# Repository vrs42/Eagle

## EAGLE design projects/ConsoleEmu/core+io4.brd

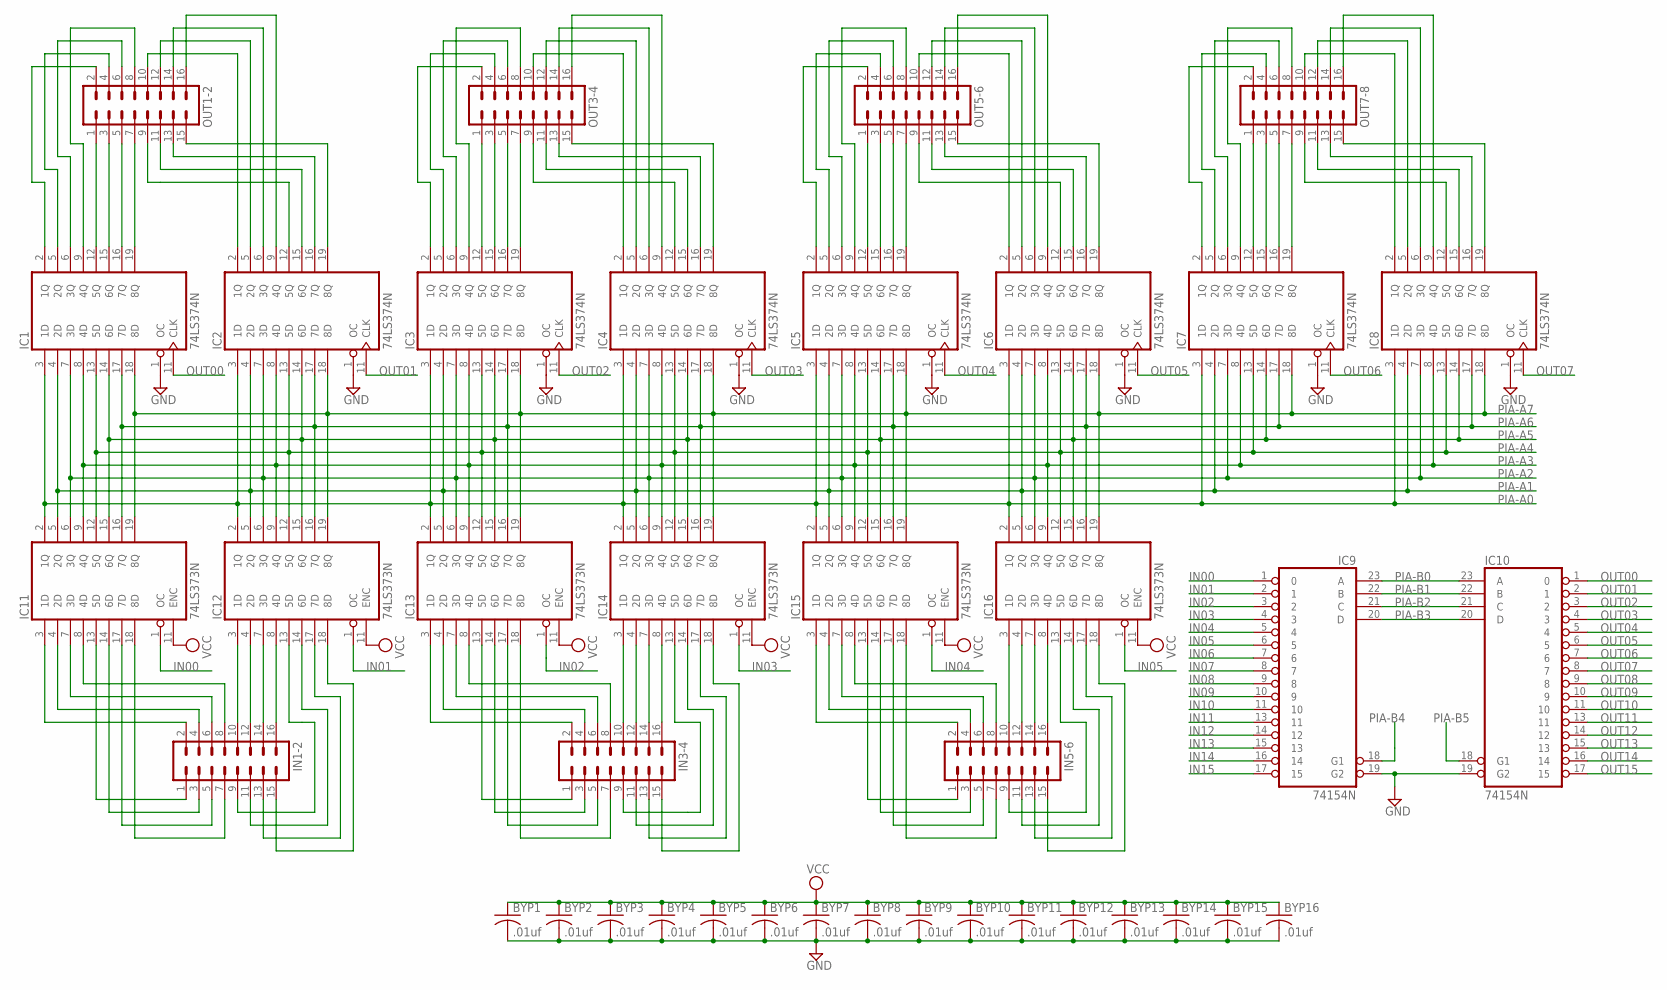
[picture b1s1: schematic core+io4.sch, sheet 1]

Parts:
BYP1, BYP2, BYP3, BYP4, BYP5, BYP6, BYP7, BYP8, BYP9, BYP10, BYP11, BYP12, BYP13, BYP14, BYP15, BYP16: .01uf; C050-025X075
IC1, IC2, IC3, IC4, IC5, IC6, IC7, IC8: 74LS374N; DIL20
IC9, IC10: 74154N; DIL24-6
IC11, IC12, IC13, IC14, IC15, IC16: 74LS373N; DIL20
IN1-2, IN3-4, IN5-6: MA08-2
OUT1-2, OUT3-4, OUT5-6, OUT7-8: MA08-2

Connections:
GND: BYP1.2, BYP2.2, BYP3.2, BYP4.2, BYP5.2, BYP6.2, BYP7.2, BYP8.2, BYP9.2, BYP10.2, BYP11.2, BYP12.2, BYP13.2, BYP14.2, BYP15.2, BYP16.2, IC1.1 (OC), IC1.10 (GND), IC2.1 (OC), IC2.10 (GND), IC3.1 (OC), IC3.10 (GND), IC4.1 (OC), IC4.10 (GND), IC5.1 (OC), IC5.10 (GND), IC6.1 (OC), IC6.10 (GND), IC7.1 (OC), IC7.10 (GND), IC8.1 (OC), IC8.10 (GND), IC9.12 (GND), IC9.19 (G2), IC10.12 (GND), IC10.19 (G2), IC11.10 (GND), IC12.10 (GND), IC13.10 (GND), IC14.10 (GND), IC15.10 (GND), IC16.10 (GND); also elsewhere on the board
IN00: IC9.1 (0), IC11.1 (OC)
IN01: IC9.2 (1), IC12.1 (OC)
IN02: IC9.3 (2), IC13.1 (OC)
IN03: IC9.4 (3), IC14.1 (OC)
IN04: IC9.5 (4), IC15.1 (OC)
IN05: IC9.6 (5), IC16.1 (OC)
IN06: IC9.7 (6)
IN07: IC9.8 (7)
IN08: IC9.9 (8)
IN09: IC9.10 (9)
IN10: IC9.11 (10)
IN11: IC9.13 (11)
IN12: IC9.14 (12)
IN13: IC9.15 (13)
IN14: IC9.16 (14)
IN15: IC9.17 (15)
unnamed: IC12.3 (1D), IN1-2.10
unnamed: IC12.4 (2D), IN1-2.12
unnamed: IC12.7 (3D), IN1-2.14
unnamed: IC12.8 (4D), IN1-2.16
unnamed: IC11.8 (4D), IN1-2.8
unnamed: IC11.7 (3D), IN1-2.6
unnamed: IC11.4 (2D), IN1-2.4
unnamed: IC11.3 (1D), IN1-2.2
unnamed: IC11.13 (5D), IN1-2.1
unnamed: IC11.14 (6D), IN1-2.3
unnamed: IC11.17 (7D), IN1-2.5
unnamed: IC11.18 (8D), IN1-2.7
unnamed: IC12.13 (5D), IN1-2.9
unnamed: IC12.14 (6D), IN1-2.11
unnamed: IC12.17 (7D), IN1-2.13
unnamed: IC12.18 (8D), IN1-2.15
unnamed: IC5.2 (1Q), OUT5-6.2
unnamed: IC14.3 (1D), IN3-4.10
unnamed: IC14.4 (2D), IN3-4.12
unnamed: IC14.7 (3D), IN3-4.14
unnamed: IC14.8 (4D), IN3-4.16
unnamed: IC3.12 (5Q), OUT3-4.1
unnamed: IC3.15 (6Q), OUT3-4.3
unnamed: IC3.16 (7Q), OUT3-4.5
unnamed: IC3.19 (8Q), OUT3-4.7
unnamed: IC13.3 (1D), IN3-4.2
unnamed: IC13.4 (2D), IN3-4.4
unnamed: IC13.7 (3D), IN3-4.6
unnamed: IC13.8 (4D), IN3-4.8
unnamed: IC14.13 (5D), IN3-4.9
unnamed: IC14.14 (6D), IN3-4.11
unnamed: IC14.17 (7D), IN3-4.13
unnamed: IC14.18 (8D), IN3-4.15
unnamed: IC13.13 (5D), IN3-4.1
unnamed: IC13.14 (6D), IN3-4.3
unnamed: IC13.17 (7D), IN3-4.5
unnamed: IC13.18 (8D), IN3-4.7
unnamed: IC3.5 (2Q), OUT3-4.4
unnamed: IC3.6 (3Q), OUT3-4.6
unnamed: IC3.2 (1Q), OUT3-4.2
unnamed: IC3.9 (4Q), OUT3-4.8
unnamed: IC1.12 (5Q), OUT1-2.1
unnamed: IC1.15 (6Q), OUT1-2.3
unnamed: IC1.16 (7Q), OUT1-2.5
unnamed: IC1.19 (8Q), OUT1-2.7
unnamed: IC1.2 (1Q), OUT1-2.2
unnamed: IC1.5 (2Q), OUT1-2.4
unnamed: IC1.6 (3Q), OUT1-2.6
unnamed: IC1.9 (4Q), OUT1-2.8
unnamed: IC2.19 (8Q), OUT1-2.15
unnamed: IC2.16 (7Q), OUT1-2.13
unnamed: IC2.15 (6Q), OUT1-2.11
unnamed: IC2.12 (5Q), OUT1-2.9
unnamed: IC2.2 (1Q), OUT1-2.10
unnamed: IC2.5 (2Q), OUT1-2.12
unnamed: IC2.6 (3Q), OUT1-2.14
unnamed: IC2.9 (4Q), OUT1-2.16
unnamed: IC4.2 (1Q), OUT3-4.10
unnamed: IC4.5 (2Q), OUT3-4.12
unnamed: IC4.6 (3Q), OUT3-4.14
unnamed: IC4.9 (4Q), OUT3-4.16
unnamed: IC4.19 (8Q), OUT3-4.15
unnamed: IC4.16 (7Q), OUT3-4.13
unnamed: IC4.15 (6Q), OUT3-4.11
unnamed: IC4.12 (5Q), OUT3-4.9
unnamed: IC16.3 (1D), IN5-6.10
unnamed: IC16.4 (2D), IN5-6.12
unnamed: IC16.7 (3D), IN5-6.14
unnamed: IC16.8 (4D), IN5-6.16
unnamed: IC5.12 (5Q), OUT5-6.1
unnamed: IC5.15 (6Q), OUT5-6.3
unnamed: IC5.16 (7Q), OUT5-6.5
unnamed: IC5.19 (8Q), OUT5-6.7
unnamed: IC7.12 (5Q), OUT7-8.1
unnamed: IC7.15 (6Q), OUT7-8.3
unnamed: IC7.16 (7Q), OUT7-8.5
unnamed: IC7.19 (8Q), OUT7-8.7
unnamed: IC5.5 (2Q), OUT5-6.4
unnamed: IC5.6 (3Q), OUT5-6.6
unnamed: IC5.9 (4Q), OUT5-6.8
unnamed: IC6.12 (5Q), OUT5-6.9
unnamed: IC6.15 (6Q), OUT5-6.11
unnamed: IC6.16 (7Q), OUT5-6.13
unnamed: IC6.19 (8Q), OUT5-6.15
unnamed: IC6.2 (1Q), OUT5-6.10
unnamed: IC6.5 (2Q), OUT5-6.12
unnamed: IC6.6 (3Q), OUT5-6.14
unnamed: IC6.9 (4Q), OUT5-6.16
unnamed: IC15.3 (1D), IN5-6.2
unnamed: IC15.4 (2D), IN5-6.4
unnamed: IC15.7 (3D), IN5-6.6
unnamed: IC15.8 (4D), IN5-6.8
unnamed: IC16.13 (5D), IN5-6.9
unnamed: IC16.14 (6D), IN5-6.11
unnamed: IC16.17 (7D), IN5-6.13
unnamed: IC16.18 (8D), IN5-6.15
unnamed: IC15.13 (5D), IN5-6.1
unnamed: IC15.14 (6D), IN5-6.3
unnamed: IC15.17 (7D), IN5-6.5
unnamed: IC15.18 (8D), IN5-6.7
unnamed: IC8.19 (8Q), OUT7-8.15
unnamed: IC8.16 (7Q), OUT7-8.13
unnamed: IC8.15 (6Q), OUT7-8.11
unnamed: IC8.12 (5Q), OUT7-8.9
unnamed: IC8.2 (1Q), OUT7-8.10
unnamed: IC8.5 (2Q), OUT7-8.12
unnamed: IC8.6 (3Q), OUT7-8.14
unnamed: IC8.9 (4Q), OUT7-8.16
unnamed: IC7.9 (4Q), OUT7-8.8
unnamed: IC7.6 (3Q), OUT7-8.6
unnamed: IC7.5 (2Q), OUT7-8.4
unnamed: IC7.2 (1Q), OUT7-8.2
OUT00: IC1.11 (CLK), IC10.1 (0)
OUT01: IC2.11 (CLK), IC10.2 (1)
OUT02: IC3.11 (CLK), IC10.3 (2)
OUT03: IC4.11 (CLK), IC10.4 (3)
OUT04: IC5.11 (CLK), IC10.5 (4)
OUT05: IC6.11 (CLK), IC10.6 (5)
OUT06: IC7.11 (CLK), IC10.7 (6)
OUT07: IC8.11 (CLK), IC10.8 (7)
OUT08: IC10.9 (8)
OUT09: IC10.10 (9)
OUT10: IC10.11 (10)
OUT11: IC10.13 (11)
OUT12: IC10.14 (12)
OUT13: IC10.15 (13)
OUT14: IC10.16 (14)
OUT15: IC10.17 (15)
PIA-A0: IC1.3 (1D), IC2.3 (1D), IC3.3 (1D), IC4.3 (1D), IC5.3 (1D), IC6.3 (1D), IC7.3 (1D), IC8.3 (1D), IC11.2 (1Q), IC12.2 (1Q), IC13.2 (1Q), IC14.2 (1Q), IC15.2 (1Q), IC16.2 (1Q); also elsewhere on the board
PIA-A1: IC1.4 (2D), IC2.4 (2D), IC3.4 (2D), IC4.4 (2D), IC5.4 (2D), IC6.4 (2D), IC7.4 (2D), IC8.4 (2D), IC11.5 (2Q), IC12.5 (2Q), IC13.5 (2Q), IC14.5 (2Q), IC15.5 (2Q), IC16.5 (2Q); also elsewhere on the board
PIA-A2: IC1.7 (3D), IC2.7 (3D), IC3.7 (3D), IC4.7 (3D), IC5.7 (3D), IC6.7 (3D), IC7.7 (3D), IC8.7 (3D), IC11.6 (3Q), IC12.6 (3Q), IC13.6 (3Q), IC14.6 (3Q), IC15.6 (3Q), IC16.6 (3Q); also elsewhere on the board
PIA-A3: IC1.8 (4D), IC2.8 (4D), IC3.8 (4D), IC4.8 (4D), IC5.8 (4D), IC6.8 (4D), IC7.8 (4D), IC8.8 (4D), IC11.9 (4Q), IC12.9 (4Q), IC13.9 (4Q), IC14.9 (4Q), IC15.9 (4Q), IC16.9 (4Q); also elsewhere on the board
PIA-A4: IC1.13 (5D), IC2.13 (5D), IC3.13 (5D), IC4.13 (5D), IC5.13 (5D), IC6.13 (5D), IC7.13 (5D), IC8.13 (5D), IC11.12 (5Q), IC12.12 (5Q), IC13.12 (5Q), IC14.12 (5Q), IC15.12 (5Q), IC16.12 (5Q); also elsewhere on the board
PIA-A5: IC1.14 (6D), IC2.14 (6D), IC3.14 (6D), IC4.14 (6D), IC5.14 (6D), IC6.14 (6D), IC7.14 (6D), IC8.14 (6D), IC11.15 (6Q), IC12.15 (6Q), IC13.15 (6Q), IC14.15 (6Q), IC15.15 (6Q), IC16.15 (6Q); also elsewhere on the board
PIA-A6: IC1.17 (7D), IC2.17 (7D), IC3.17 (7D), IC4.17 (7D), IC5.17 (7D), IC6.17 (7D), IC7.17 (7D), IC8.17 (7D), IC11.16 (7Q), IC12.16 (7Q), IC13.16 (7Q), IC14.16 (7Q), IC15.16 (7Q), IC16.16 (7Q); also elsewhere on the board
PIA-A7: IC1.18 (8D), IC2.18 (8D), IC3.18 (8D), IC4.18 (8D), IC5.18 (8D), IC6.18 (8D), IC7.18 (8D), IC8.18 (8D), IC11.19 (8Q), IC12.19 (8Q), IC13.19 (8Q), IC14.19 (8Q), IC15.19 (8Q), IC16.19 (8Q); also elsewhere on the board
PIA-B0: IC9.23 (A), IC10.23 (A); also elsewhere on the board
PIA-B1: IC9.22 (B), IC10.22 (B); also elsewhere on the board
PIA-B2: IC9.21 (C), IC10.21 (C); also elsewhere on the board
PIA-B3: IC9.20 (D), IC10.20 (D); also elsewhere on the board
PIA-B4: IC9.18 (G1); also elsewhere on the board
PIA-B5: IC10.18 (G1); also elsewhere on the board
VCC: BYP1.1, BYP2.1, BYP3.1, BYP4.1, BYP5.1, BYP6.1, BYP7.1, BYP8.1, BYP9.1, BYP10.1, BYP11.1, BYP12.1, BYP13.1, BYP14.1, BYP15.1, BYP16.1, IC1.20 (VCC), IC2.20 (VCC), IC3.20 (VCC), IC4.20 (VCC), IC5.20 (VCC), IC6.20 (VCC), IC7.20 (VCC), IC8.20 (VCC), IC9.24 (VCC), IC10.24 (VCC), IC11.11 (ENC), IC11.20 (VCC), IC12.11 (ENC), IC12.20 (VCC), IC13.11 (ENC), IC13.20 (VCC), IC14.11 (ENC), IC14.20 (VCC), IC15.11 (ENC), IC15.20 (VCC), IC16.11 (ENC), IC16.20 (VCC); also elsewhere on the board

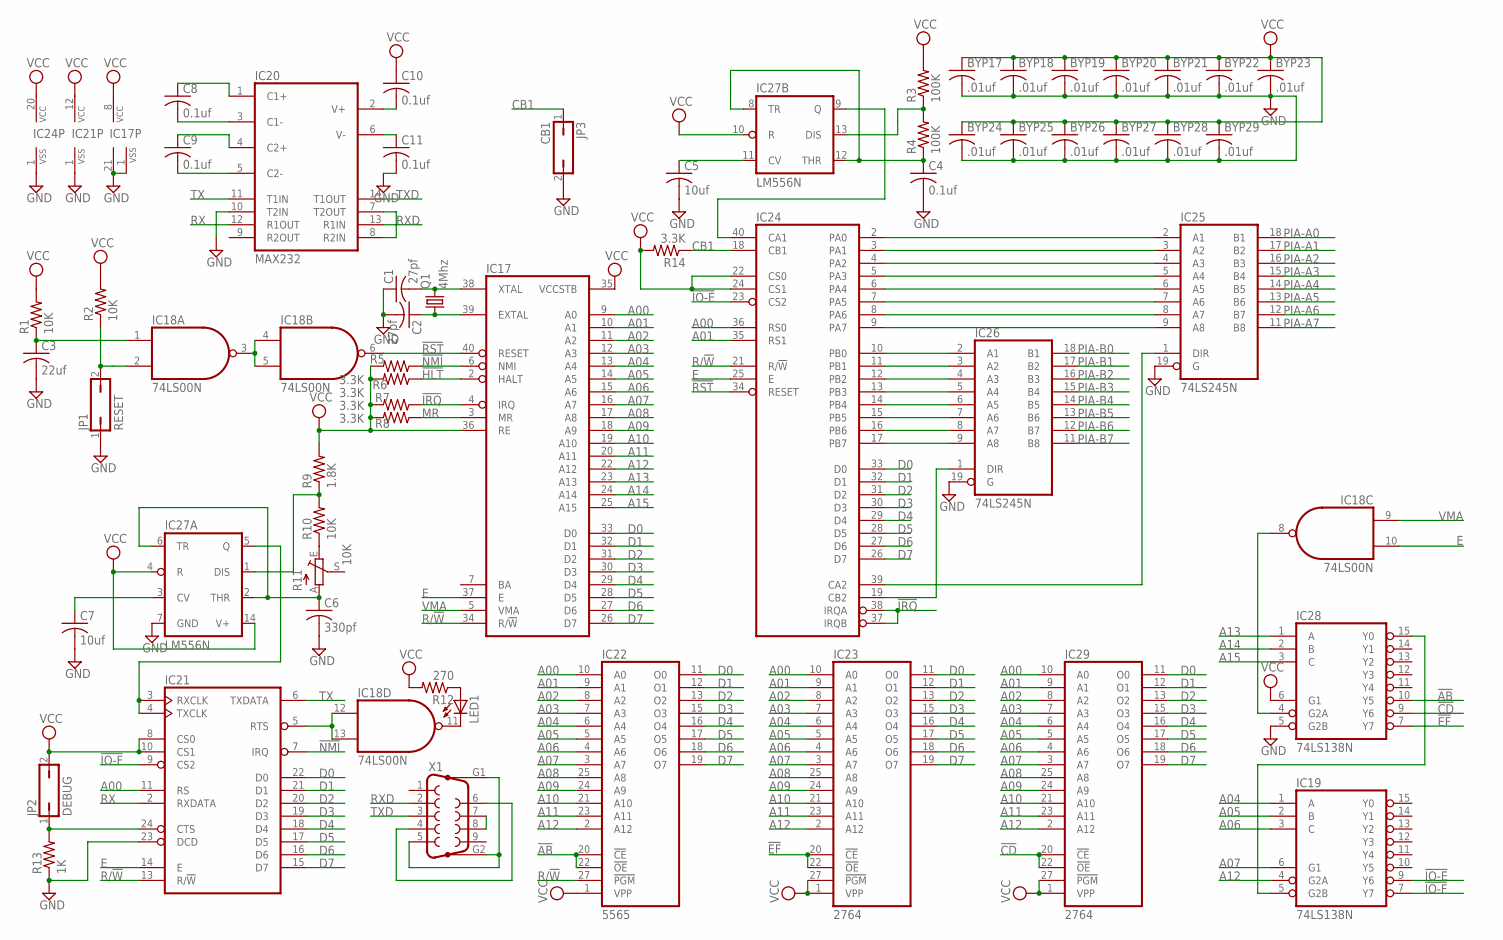
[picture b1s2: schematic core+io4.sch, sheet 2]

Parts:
BYP17, BYP18, BYP19, BYP20, BYP21, BYP22, BYP23, BYP24, BYP25, BYP26, BYP27, BYP28, BYP29: .01uf; C050-025X075
C1, C2: 27pf; C050-025X075
C3: 22uf; C102-043X133
C4, C8, C9, C10, C11: 0.1uf; C050-025X075
C5, C7: 10uf; C050-025X075
C6: 330pf; C050-025X075
IC17: 6802; DIL40
IC18: 74LS00N; DIL14
IC19, IC28: 74LS138N; DIL16
IC20: MAX232; DIL16
IC21: 6850; DIL24
IC22: 5565; DIL28
IC23, IC29: 2764; DIL28
IC24: 6821; DIL40
IC25, IC26: 74LS245N; DIL20
IC27: LM556N; DIL14
JP1: RESET; JP1
JP2: DEBUG; JP1
JP3: CB1; JP1
LED1: LED3MM
Q1: 4Mhz; HC18U-V
R1, R2, R10: 10K; 0207/7
R3, R4: 100K; 0207/7
R5, R6, R7, R8, R14: 3.3K; 0207/7
R9: 1.8K; 0207/7
R11: 10K; SP19L
R12: 270; 0207/7
R13: 1K; 0207/7
X1: F09HP

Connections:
!AB: IC22.20 (!CE), IC22.22 (!OE), IC28.10 (Y5)
!CD: IC28.9 (Y6), IC29.20 (!CE), IC29.22 (!OE)
!EF: IC23.20 (!CE), IC23.22 (!OE), IC28.7 (Y7)
!HLT: IC17.2 (HALT), R5.1
!IO-E: IC19.9 (Y6), IC24.23 (CS2)
!IO-F: IC19.7 (Y7), IC21.9 (CS2)
!IRQ: IC17.4 (IRQ), IC24.37 (IRQB), IC24.38 (IRQA), R7.1
!NMI: IC17.6 (NMI), IC21.7 (IRQ), R6.1
!RST: IC17.40 (RESET), IC18.6 (O), IC24.34 (RESET)
A00: IC17.9 (A0), IC21.11 (RS), IC22.10 (A0), IC23.10 (A0), IC24.36 (RS0), IC29.10 (A0)
A01: IC17.10 (A1), IC22.9 (A1), IC23.9 (A1), IC24.35 (RS1), IC29.9 (A1)
A02: IC17.11 (A2), IC22.8 (A2), IC23.8 (A2), IC29.8 (A2)
A03: IC17.12 (A3), IC22.7 (A3), IC23.7 (A3), IC29.7 (A3)
A04: IC17.13 (A4), IC19.1 (A), IC22.6 (A4), IC23.6 (A4), IC29.6 (A4)
A05: IC17.14 (A5), IC19.2 (B), IC22.5 (A5), IC23.5 (A5), IC29.5 (A5)
A06: IC17.15 (A6), IC19.3 (C), IC22.4 (A6), IC23.4 (A6), IC29.4 (A6)
A07: IC17.16 (A7), IC19.6 (G1), IC22.3 (A7), IC23.3 (A7), IC29.3 (A7)
A08: IC17.17 (A8), IC22.25 (A8), IC23.25 (A8), IC29.25 (A8)
A09: IC17.18 (A9), IC22.24 (A9), IC23.24 (A9), IC29.24 (A9)
A10: IC17.19 (A10), IC22.21 (A10), IC23.21 (A10), IC29.21 (A10)
A11: IC17.20 (A11), IC22.23 (A11), IC23.23 (A11), IC29.23 (A11)
A12: IC17.22 (A12), IC19.4 (G2A), IC22.2 (A12), IC23.2 (A12), IC29.2 (A12)
A13: IC17.23 (A13), IC28.1 (A)
A14: IC17.24 (A14), IC28.2 (B)
A15: IC17.25 (A15), IC28.3 (C)
CB1: IC24.18 (CB1), JP3.1, R14.1
D0: IC17.33 (D0), IC21.22 (D0), IC22.11 (O0), IC23.11 (O0), IC24.33 (D0), IC29.11 (O0)
D1: IC17.32 (D1), IC21.21 (D1), IC22.12 (O1), IC23.12 (O1), IC24.32 (D1), IC29.12 (O1)
D2: IC17.31 (D2), IC21.20 (D2), IC22.13 (O2), IC23.13 (O2), IC24.31 (D2), IC29.13 (O2)
D3: IC17.30 (D3), IC21.19 (D3), IC22.15 (O3), IC23.15 (O3), IC24.30 (D3), IC29.15 (O3)
D4: IC17.29 (D4), IC21.18 (D4), IC22.16 (O4), IC23.16 (O4), IC24.29 (D4), IC29.16 (O4)
D5: IC17.28 (D5), IC21.17 (D5), IC22.17 (O5), IC23.17 (O5), IC24.28 (D5), IC29.17 (O5)
D6: IC17.27 (D6), IC21.16 (D6), IC22.18 (O6), IC23.18 (O6), IC24.27 (D6), IC29.18 (O6)
D7: IC17.26 (D7), IC21.15 (D7), IC22.19 (O7), IC23.19 (O7), IC24.26 (D7), IC29.19 (O7)
E: IC17.37 (E), IC18.10 (I1), IC21.14 (E), IC24.25 (E)
GND: BYP17.2, BYP18.2, BYP19.2, BYP20.2, BYP21.2, BYP22.2, BYP23.2, BYP24.2, BYP25.2, BYP26.2, BYP27.2, BYP28.2, BYP29.2, C1.1, C2.2, C3.2, C4.2, C5.2, C6.2, C7.2, C11.2, IC17.1 (VSS), IC17.21 (VSS), IC18.7 (GND), IC19.8 (GND), IC20.10 (T2IN), IC20.15 (GND), IC21.1 (VSS), IC21.23 (DCD), IC22.14 (GND), IC23.14 (GND), IC24.1 (VSS), IC25.10 (GND), IC25.19 (G), IC26.10 (GND), IC26.19 (G), IC27.7 (GND), IC28.5 (G2B), IC28.8 (GND), IC29.14 (GND), JP1.1, JP3.2, R13.1; also elsewhere on the board
MR: IC17.3 (MR), R8.1
unnamed: C2.1, IC17.39 (EXTAL), Q1.1
unnamed: C1.2, IC17.38 (XTAL), Q1.2
unnamed: IC24.2 (PA0), IC25.2 (A1)
unnamed: IC18.3 (O), IC18.4 (I0), IC18.5 (I1)
unnamed: C3.1, IC18.1 (I0), R1.1
unnamed: IC18.2 (I1), JP1.2, R2.1
unnamed: IC21.3 (RXCLK), IC21.4 (TXCLK), IC27.5 (Q)
unnamed: IC24.10 (PB0), IC26.2 (A1)
unnamed: IC24.11 (PB1), IC26.3 (A2)
unnamed: C6.1, IC27.2 (THR), IC27.6 (TR), R11.A
unnamed: IC27.1 (DIS), R9.1, R10.2
unnamed: IC24.12 (PB2), IC26.4 (A3)
unnamed: IC24.13 (PB3), IC26.5 (A4)
unnamed: IC24.14 (PB4), IC26.6 (A5)
unnamed: IC24.15 (PB5), IC26.7 (A6)
unnamed: IC24.16 (PB6), IC26.8 (A7)
unnamed: IC24.17 (PB7), IC26.9 (A8)
unnamed: IC24.3 (PA1), IC25.3 (A2)
unnamed: IC24.4 (PA2), IC25.4 (A3)
unnamed: IC24.5 (PA3), IC25.5 (A4)
unnamed: IC24.6 (PA4), IC25.6 (A5)
unnamed: IC24.7 (PA5), IC25.7 (A6)
unnamed: IC24.8 (PA6), IC25.8 (A7)
unnamed: IC24.9 (PA7), IC25.9 (A8)
unnamed: IC24.19 (CB2), IC26.1 (DIR)
unnamed: IC24.39 (CA2), IC25.1 (DIR)
unnamed: IC24.40 (CA1), IC27.9 (Q)
unnamed: C4.1, IC27.8 (TR), IC27.12 (THR), R4.1
unnamed: IC27.13 (DIS), R3.1, R4.2
unnamed: C5.1, IC27.11 (CV)
unnamed: R10.1, R11.E
unnamed: X1.4, X1.6
unnamed: X1.7, X1.8
unnamed: X1.5, X1.G1, X1.G2
unnamed: IC18.12 (I0), IC18.13 (I1), IC21.5 (RTS)
unnamed: IC18.11 (O), LED1.K (C)
unnamed: LED1.A, R12.1
unnamed: IC21.24 (CTS), JP2.1, R13.2
unnamed: IC18.8 (O), IC28.4 (G2A)
unnamed: IC19.5 (G2B), IC28.15 (Y0)
unnamed: IC20.7 (T2OUT), IC20.8 (R2IN)
unnamed: C7.1, IC27.3 (CV)
unnamed: C9.2, IC20.5 (C2-)
unnamed: C9.1, IC20.4 (C2+)
unnamed: C8.2, IC20.3 (C1-)
unnamed: C8.1, IC20.1 (C1+)
unnamed: C11.1, IC20.6 (V-)
unnamed: C10.2, IC20.2 (V+)
PIA-A0: IC25.18 (B1); also elsewhere on the board
PIA-A1: IC25.17 (B2); also elsewhere on the board
PIA-A2: IC25.16 (B3); also elsewhere on the board
PIA-A3: IC25.15 (B4); also elsewhere on the board
PIA-A4: IC25.14 (B5); also elsewhere on the board
PIA-A5: IC25.13 (B6); also elsewhere on the board
PIA-A6: IC25.12 (B7); also elsewhere on the board
PIA-A7: IC25.11 (B8); also elsewhere on the board
PIA-B0: IC26.18 (B1); also elsewhere on the board
PIA-B1: IC26.17 (B2); also elsewhere on the board
PIA-B2: IC26.16 (B3); also elsewhere on the board
PIA-B3: IC26.15 (B4); also elsewhere on the board
PIA-B4: IC26.14 (B5); also elsewhere on the board
PIA-B5: IC26.13 (B6); also elsewhere on the board
PIA-B6: IC26.12 (B7); also elsewhere on the board
PIA-B7: IC26.11 (B8); also elsewhere on the board
R/!W: IC17.34 (R/!W), IC21.13 (R/!W), IC22.27 (!PGM), IC24.21 (R/!W)
RX: IC20.12 (R1OUT), IC21.2 (RXDATA)
RXD: IC20.13 (R1IN), X1.2
TX: IC20.11 (T1IN), IC21.6 (TXDATA)
TXD: IC20.14 (T1OUT), X1.3
VCC: BYP17.1, BYP18.1, BYP19.1, BYP20.1, BYP21.1, BYP22.1, BYP23.1, BYP24.1, BYP25.1, BYP26.1, BYP27.1, BYP28.1, BYP29.1, C10.1, IC17.8 (VCC), IC17.35 (VCCSTB), IC17.36 (RE), IC18.14 (VCC), IC19.16 (VCC), IC20.16 (VCC), IC21.8 (CS0), IC21.10 (CS1), IC21.12 (VCC), IC22.1 (VPP), IC22.28 (VCC), IC23.1 (VPP), IC23.27 (!PGM), IC23.28 (VCC), IC24.20 (VCC), IC24.22 (CS0), IC24.24 (CS1), IC25.20 (VCC), IC26.20 (VCC), IC27.4 (R), IC27.10 (R), IC27.14 (V+), IC28.6 (G1), IC28.16 (VCC), IC29.1 (VPP), IC29.27 (!PGM), IC29.28 (VCC), JP2.2, R1.2, R2.2, R3.2, R5.2, R6.2, R7.2, R8.2, R9.2, R12.2, R14.2; also elsewhere on the board
VMA: IC17.5 (VMA), IC18.9 (I0)

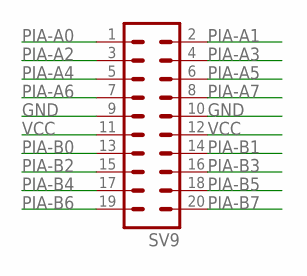
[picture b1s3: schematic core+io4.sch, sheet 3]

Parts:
SV9: MA10-2

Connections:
GND: SV9.9, SV9.10; also elsewhere on the board
PIA-A0: SV9.1; also elsewhere on the board
PIA-A1: SV9.2; also elsewhere on the board
PIA-A2: SV9.3; also elsewhere on the board
PIA-A3: SV9.4; also elsewhere on the board
PIA-A4: SV9.5; also elsewhere on the board
PIA-A5: SV9.6; also elsewhere on the board
PIA-A6: SV9.7; also elsewhere on the board
PIA-A7: SV9.8; also elsewhere on the board
PIA-B0: SV9.13; also elsewhere on the board
PIA-B1: SV9.14; also elsewhere on the board
PIA-B2: SV9.15; also elsewhere on the board
PIA-B3: SV9.16; also elsewhere on the board
PIA-B4: SV9.17; also elsewhere on the board
PIA-B5: SV9.18; also elsewhere on the board
PIA-B6: SV9.19; also elsewhere on the board
PIA-B7: SV9.20; also elsewhere on the board
VCC: SV9.11, SV9.12; also elsewhere on the board

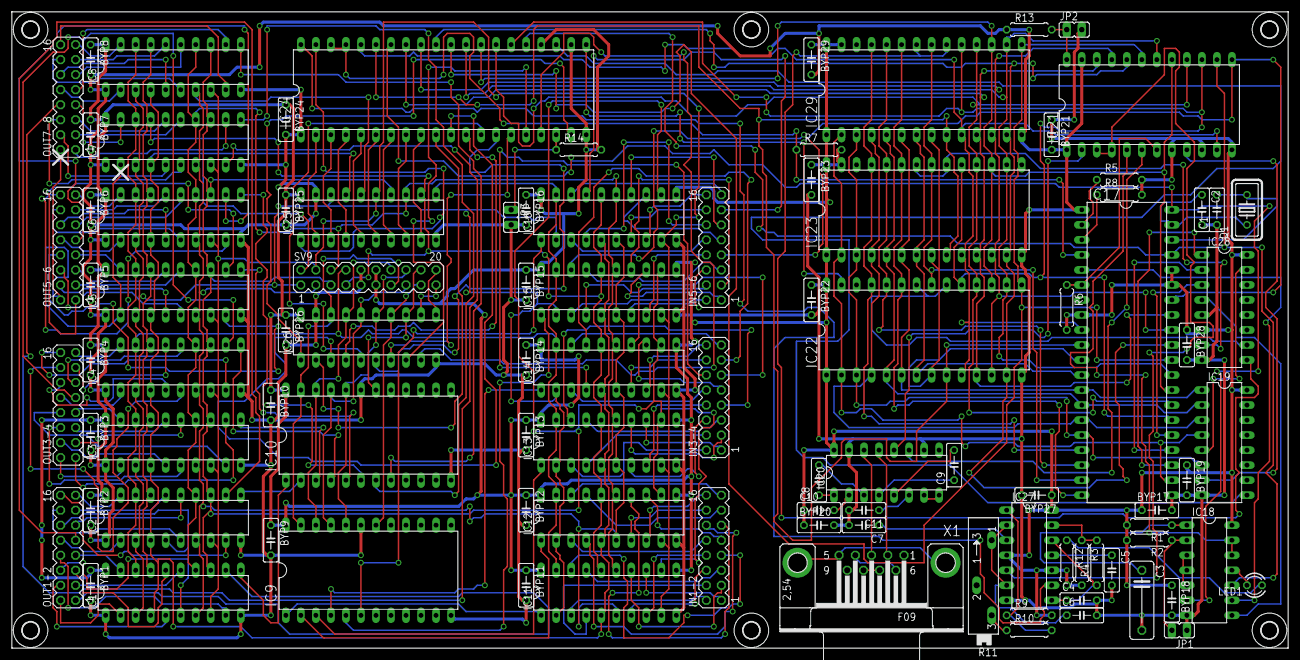
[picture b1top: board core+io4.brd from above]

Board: 2 copper layers, 215.9 x 107.6 mm, 103 parts (0 on the bottom side), 234 nets.

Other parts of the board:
U$1, U$2, U$3, U$4, U$5, U$6: 2,8

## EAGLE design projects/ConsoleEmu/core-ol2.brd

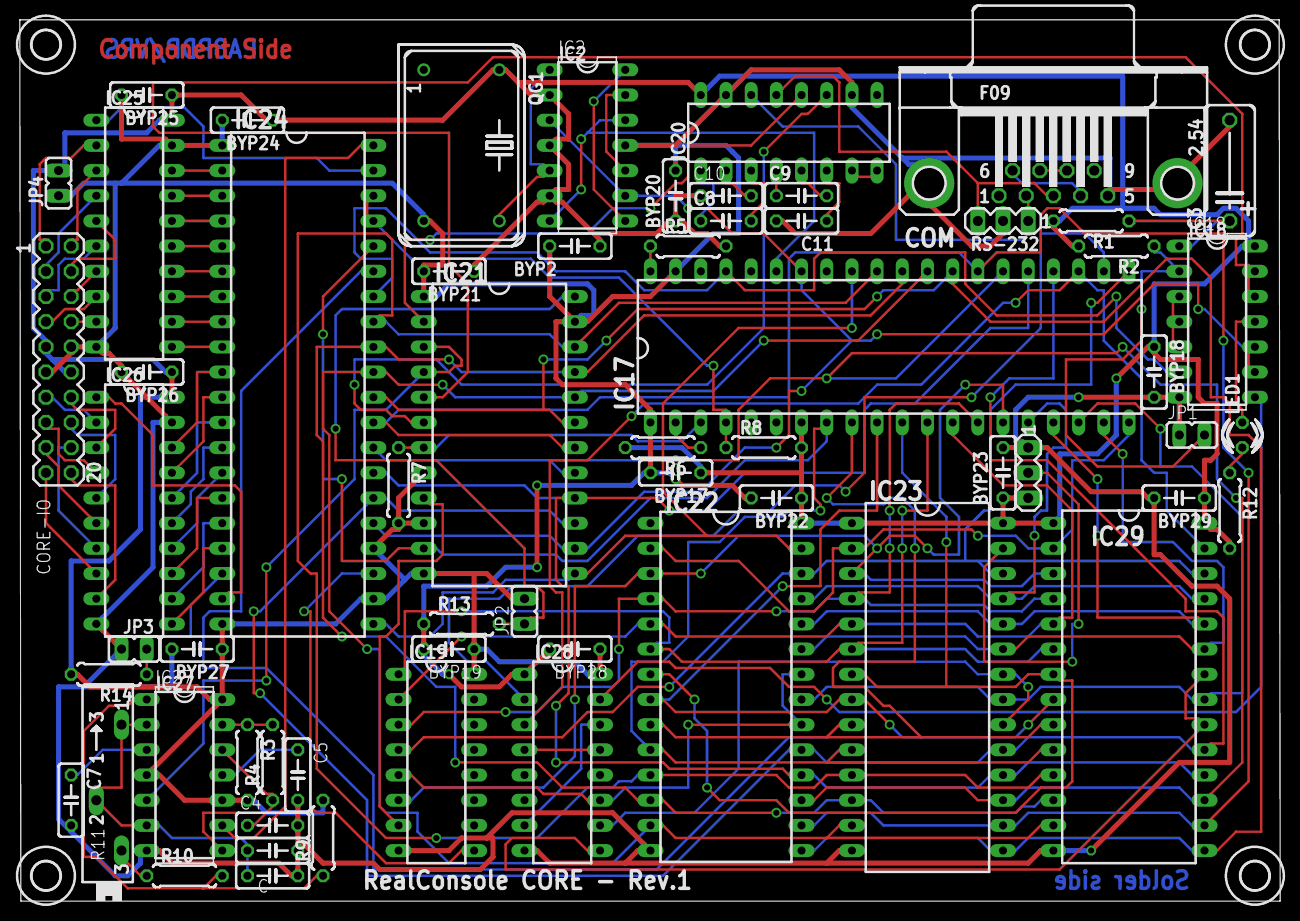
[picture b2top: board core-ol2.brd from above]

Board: 2 copper layers, 127.1 x 88.9 mm, 66 parts (0 on the bottom side), 110 nets.

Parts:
BYP2, BYP17, BYP18, BYP19, BYP20, BYP21, BYP22, BYP23, BYP24, BYP25, BYP26, BYP27, BYP28, BYP29: .01uf; C050-025X075
C: C050-025X075
C3: 22uf; C102-054X133
C4, C8, C9, C10, C11: 0.1uf; C050-025X075
C5, C7: .01uf; C050-025X075
C6: 220pf; C050-025X075
COM: F09HP
CORE-IO: MA10-2
EP-1: MA03-1
IC2: 74LS73N; DIL14
IC17: 6809E; DIL40
IC18: 74LS132N; DIL14
IC19: 74LS138N; DIL16
IC20: MAX232; DIL16
IC21: 6850; DIL24
IC22: 6264A; DIL28-6
IC23: 27C128P; DIL28-6
IC24: 6821; DIL40
IC25, IC26: 74LS245N; DIL20
IC27: LM556N; DIL14
IC28: 74LS139N; DIL16
IC29: 27256; DIL28
JP1: RESET; JP1
JP2: DEBUG; JP1
JP3: CB1; JP1
JP4: POWER; JP1
LED1: LED3MM
QG1: 4Mhz; DIL14S
R1, R2, R10: 10K; 0207/7
R3, R4: 100K; 0207/7
R5, R6, R7, R8, R9, R14: 3.3K; 0207/7
R11: 10K; SP19L
R12: 270; 0207/7
R13: 1K; 0207/7
RS-232: MA03-1
U$3, U$4, U$5, U$6: 2,8

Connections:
!4-B: IC28.9, IC29.20, IC29.22
!0123: IC19.5, IC22.20, IC22.22, IC28.11
!CDEF: IC23.20, IC23.22, IC28.10
!EP1: IC28.7, IC28.14
!FIRQ: IC17.4, IC24.37, IC24.38, R8.1
!HLT: IC17.40, R5.1
!IO-E: IC19.9, IC24.23
!IO-F: IC19.7, IC21.9
!IRQ: IC17.3, IC21.7, R7.1
!NMI: IC17.2, R6.1
!RST: IC17.37, IC18.6, IC24.34
A00: IC17.8, IC21.11, IC22.10, IC23.10, IC24.36, IC29.10
A01: IC17.9, IC22.9, IC23.9, IC24.35, IC29.9
A02: IC17.10, IC22.8, IC23.8, IC29.8
A03: IC17.11, IC22.7, IC23.7, IC29.7
A04: IC17.12, IC19.1, IC22.6, IC23.6, IC29.6
A05: IC17.13, IC19.2, IC22.5, IC23.5, IC29.5
A06: IC17.14, IC19.3, IC22.4, IC23.4, IC29.4
A07: IC17.15, IC19.6, IC22.3, IC23.3, IC29.3
A08: IC17.16, IC22.25, IC23.25, IC29.25
A09: IC17.17, IC22.24, IC23.24, IC29.24
A10: IC17.18, IC22.21, IC23.21, IC29.21
A11: IC17.19, IC22.23, IC23.23, IC29.23
A12: IC17.20, IC22.2, IC23.2, IC29.2
A13: IC17.21, IC19.4, IC22.26, IC23.26, IC29.26
A14: IC17.22, IC28.2
A15: IC17.23, IC28.3, IC29.27
CB1: IC24.18, JP3.2, R14.1
D0: IC17.31, IC21.22, IC22.11, IC23.11, IC24.33, IC29.11
D1: IC17.30, IC21.21, IC22.12, IC23.12, IC24.32, IC29.12
D2: IC17.29, IC21.20, IC22.13, IC23.13, IC24.31, IC29.13
D3: IC17.28, IC21.19, IC22.15, IC23.15, IC24.30, IC29.15
D4: IC17.27, IC21.18, IC22.16, IC23.16, IC24.29, IC29.16
D5: IC17.26, IC21.17, IC22.17, IC23.17, IC24.28, IC29.17
D6: IC17.25, IC21.16, IC22.18, IC23.18, IC24.27, IC29.18
D7: IC17.24, IC21.15, IC22.19, IC23.19, IC24.26, IC29.19
E: IC2.3, IC2.9, IC17.34, IC18.9, IC18.10, IC21.14, IC24.25
EP: IC28.4, IC28.13
GND: BYP2.2, BYP17.2, BYP18.2, BYP19.2, BYP20.2, BYP21.2, BYP22.2, BYP23.2, BYP24.2, BYP25.2, BYP26.2, BYP27.2, BYP28.2, BYP29.2, C.2, C3.2, C4.2, C5.2, C6.2, C7.2, C11.2, COM.5, COM.G1, COM.G2, CORE-IO.10, CORE-IO.11, EP-1.1, IC2.11, IC17.1, IC17.39, IC18.7, IC19.8, IC20.10, IC20.15, IC21.1, IC21.23, IC22.14, IC23.14, IC24.1, IC25.10, IC25.19, IC26.10, IC26.19, IC27.7, IC28.1, IC28.8, IC29.14, JP1.1, JP3.1, JP4.1, QG1.7, R13.1, RS-232.2
unnamed: COM.4, COM.6
unnamed: IC2.1, IC2.5, QG1.8
unnamed: IC2.10, IC2.13
unnamed: EP-1.2, IC23.27
unnamed: IC24.2, IC25.18
unnamed: IC18.3, IC18.4, IC18.5
unnamed: IC2.8, IC2.14
unnamed: C3.1, IC18.1, R1.1
unnamed: IC18.2, JP1.2, R2.1
unnamed: IC21.3, IC21.4, IC27.5
unnamed: IC24.10, IC26.18
unnamed: IC24.11, IC26.17
unnamed: C.1, C6.1, IC27.2, IC27.6, R11.A, R11.S
unnamed: IC27.1, R9.1, R10.2
unnamed: IC24.12, IC26.16
unnamed: IC24.13, IC26.15
unnamed: IC24.14, IC26.14
unnamed: IC24.15, IC26.13
unnamed: IC24.16, IC26.12
unnamed: IC24.17, IC26.11
unnamed: IC24.3, IC25.17
unnamed: IC24.4, IC25.16
unnamed: IC24.5, IC25.15
unnamed: IC24.6, IC25.14
unnamed: IC24.7, IC25.13
unnamed: IC24.8, IC25.12
unnamed: IC24.9, IC25.11
unnamed: IC24.19, IC26.1
unnamed: IC24.39, IC25.1
unnamed: IC24.40, IC27.9
unnamed: C4.1, IC27.8, IC27.12, R4.1
unnamed: IC27.13, R3.1, R4.2
unnamed: C5.1, IC27.11
unnamed: R10.1, R11.E
unnamed: COM.7, COM.8
unnamed: IC18.12, IC18.13, IC21.5
unnamed: IC18.11, LED1.K
unnamed: LED1.A, R12.1
unnamed: IC21.24, JP2.1, R13.2
unnamed: IC18.8, IC28.15
unnamed: IC20.7, IC20.8
unnamed: C7.1, IC27.3
unnamed: C9.2, IC20.5
unnamed: C9.1, IC20.4
unnamed: C8.2, IC20.3
unnamed: C8.1, IC20.1
unnamed: C11.1, IC20.6
unnamed: C10.2, IC20.2
PIA-A0: CORE-IO.1, IC25.2
PIA-A1: CORE-IO.2, IC25.3
PIA-A2: CORE-IO.3, IC25.4
PIA-A3: CORE-IO.4, IC25.5
PIA-A4: CORE-IO.5, IC25.6
PIA-A5: CORE-IO.6, IC25.7
PIA-A6: CORE-IO.7, IC25.8
PIA-A7: CORE-IO.8, IC25.9
PIA-B0: CORE-IO.13, IC26.2
PIA-B1: CORE-IO.14, IC26.3
PIA-B2: CORE-IO.15, IC26.4
PIA-B3: CORE-IO.16, IC26.5
PIA-B4: CORE-IO.17, IC26.6
PIA-B5: CORE-IO.18, IC26.7
PIA-B6: CORE-IO.19, IC26.8
PIA-B7: CORE-IO.20, IC26.9
Q: IC2.7, IC2.12, IC17.35
R/!W: IC17.32, IC21.13, IC22.27, IC24.21
RX: IC20.12, IC21.2
RXD: COM.3, IC20.13, RS-232.3
TX: IC20.11, IC21.6
TXD: COM.2, IC20.14, RS-232.1
VCC: BYP2.1, BYP17.1, BYP18.1, BYP19.1, BYP20.1, BYP21.1, BYP22.1, BYP23.1, BYP24.1, BYP25.1, BYP26.1, BYP27.1, BYP28.1, BYP29.1, C10.1, CORE-IO.9, CORE-IO.12, EP-1.3, IC2.2, IC2.4, IC2.6, IC17.7, IC18.14, IC19.16, IC20.16, IC21.8, IC21.10, IC21.12, IC22.28, IC23.1, IC23.28, IC24.20, IC24.22, IC24.24, IC25.20, IC26.20, IC27.4, IC27.10, IC27.14, IC28.16, IC29.1, IC29.28, JP2.2, JP4.2, QG1.14, R1.2, R2.2, R3.2, R5.2, R6.2, R7.2, R8.2, R9.2, R12.2, R14.2
